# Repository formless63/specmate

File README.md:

A self-hosted engineering workshop for reusable parts, boards, cables, enclosures,
firmware, assemblies, and the physical things built from them.

Define an item once. Pin its exact revision wherever it is used. Carry its sources,
identity and evidence through drawings, build documents, jobs and physical units.
Humans and authorized agents use the same controlled operations.

**Pre-1.0, under active development.** The application is usable from a source-built
installation. Engineering coverage and native-tool support vary by workflow; the
[capability catalog](spec/capabilities.json) describes intended requirements, not a
claim that every capability is qualified. There is no supported stable release yet.

## Inside the workshop

- **A reusable Library:** typed records, immutable revisions, exact references, Where used,
  project collections, searchable identifiers and retained sources.
- **Cables and harnesses:** connector faces, conductor mapping, manual graph editing,
  stock cross-sections and 3D inspection, preparation and test documents.
- **Boards and devices:** declared board connectivity, source-linked native intake,
  component populations, firmware targets, assembly trees and scene inspection.
- **Make and evidence:** BOM and material plans, stock reservations and consumption,
  physical units, retained documents, build receipts and reviewed evidence.
- **Controlled automation:** session-based APIs and MCP, durable Temporal workflows,
  and optional isolated runners with explicit tool and recipe approval.

Unknown dimensions and unverified behavior stay visible. A successful render, check or
build is not physical qualification. See the [product specification](docs/PRODUCT.md)
and [engineering model](docs/DOMAIN.md).

## A look around

The screenshots below show actual application views with synthetic demonstration data.
They do not show customer designs or establish physical qualification.

| Wire-stock construction | Board connectivity |
| --- | --- |
|  |  |

[Screenshot provenance](docs/assets/screenshots/README.md).

## Run it yourself

You need Linux, Docker Engine with the Compose plugin, Git and Python 3. Images are
built from this checkout; no published Specmate image or external account is required.
From a clone of this repository:

```bash
specmate_stack="$HOME/stacks/specmate"
install -d -m 0700 "$specmate_stack"
cp compose.example.yaml "$specmate_stack/compose.yaml"
python3 deploy/configure.py --output "$specmate_stack/.env"
cd "$specmate_stack"
docker compose config -q
docker compose build
docker compose up -d --wait
docker compose exec app python manage.py owner_setup_token
```

Open **http://localhost:8080**, enter the single-use setup token and create your local
owner account. Temporal's operator UI is at http://localhost:8081. Both bind to loopback
by default. Keep the generated `.env` and persistent volumes: they belong to this
installation. The configuration generator refuses to overwrite existing credentials.
The default Compose names are fixed; use a dedicated Docker host or review names,
ports and volumes before running more than one installation.

The [installation guide](deploy/README.md) covers readiness, HTTPS/reverse proxies,
backup and same-version restore, and optional native execution. Build downloads require
network access to pinned image and dependency registries. Native execution is disabled
until explicitly configured; importing a source does not execute it.

## Architecture and contributing

Django/Python owns engineering operations and authorization. React/TypeScript provides
the interface; PostgreSQL and a content-addressed artifact store retain state; Temporal
coordinates durable jobs. The default installation has six services and an optional
runner. No SaaS, AI provider, ERP or email provider is a required dependency.
See [architecture](docs/ARCHITECTURE.md).

Start with [CONTRIBUTING.md](CONTRIBUTING.md), [AGENTS.md](AGENTS.md), the
[documentation map](docs/README.md), and [development commands](docs/DEVELOPMENT.md).
The lightweight repository checks need Python 3.11 or later:

```bash
python3 scripts/check_guidance.py
python3 scripts/check_public_tree.py
```

Before v1.0.0 there is no historical development-schema compatibility promise. Original
sources and real installation data are never implicitly disposable. See the
[development policy](docs/DEVELOPMENT.md).

## Rights

The original application code and documentation are AGPL-3.0-only unless a file declares
otherwise. Third-party code and engineering assets retain their terms. See
[LICENSING.md](LICENSING.md) and [NOTICE](NOTICE).

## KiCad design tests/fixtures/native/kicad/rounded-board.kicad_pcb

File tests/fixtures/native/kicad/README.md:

# Original synthetic KiCad fixtures

`two-net-board.kicad_pcb` is an original, deliberately simple board authored by
`toolpacks/kicad/generate_fixture.py` using the pinned KiCad 10.0.6 image. It uses
embedded original footprints, no external library assets, and stable UUIDs.
The native board format is `20260206`. The fixture files and generator use the
repository's AGPL-3.0-only license.

The board has a 40 × 25 mm outline, 1.6 mm thickness, and four unplated 2 mm
mounting holes at (3, 3), (37, 3), (3, 22), and (37, 22) mm. J1 and R1 each have
two 2 × 2 mm pads. Two 0.5 mm tracks run horizontally from x=10 to x=25 mm at
y=10 and y=15 mm. The first connects J1.1 to R1.1 on N1; the second connects
J1.2 to R1.2 on N2. R1 has value `1k`; its component passage remains separate
from the copper nets. Coordinates follow KiCad's x-right, y-down frame.

The acceptance facts live independently in `tests/fixtures/board-expectations.json`.
The generator does not read that expectation file, and the checker must derive
facts from the native board before comparing them. Preserve that separation when
changing either side. Successful DRC does not qualify a physical design; there is
no schematic, sourced component, electrical rating or manufacturing process here.

`invalid-board.kicad_pcb` deliberately has an unknown item and an unclosed root.
It exercises rejection by the real parser; it is not a valid engineering source.
Do not repair it into a successful input.

See `toolpacks/kicad/README.md` for the pinned environment and regeneration.

`rounded-board.kicad_pcb` is the same original board with a different `Edge.Cuts`
outline: a 40 × 25 mm rectangle with four 4 mm radius corner arcs (arcs authored
as start, mid, end) and one 3 mm radius circular cutout centerd at (20, 12.5) mm.
Expected exact values are derived analytically in `backend/tests/test_pcb_outline_arcs.py`:
net area = 1000 − 4·(4 − π)·4² − π·3² mm², bounds 0, 0 to 40, 25.

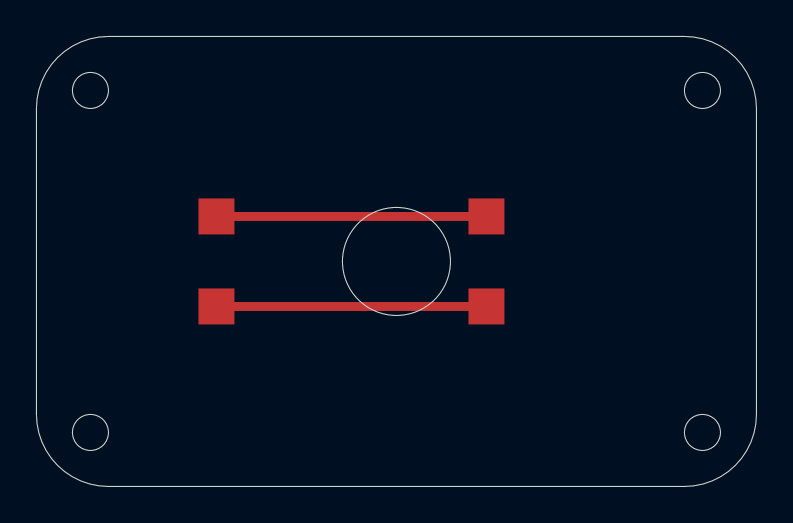
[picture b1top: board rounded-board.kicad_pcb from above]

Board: 2 copper layers, 40.0 x 25.0 mm, 6 parts (0 on the bottom side), 2 nets.

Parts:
H1: MountingHole_2mm; Synthetic_H1
H2: MountingHole_2mm; Synthetic_H2
H3: MountingHole_2mm; Synthetic_H3
H4: MountingHole_2mm; Synthetic_H4
J1: CONN_2; Synthetic_J1
R1: 1k; Synthetic_R1

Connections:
N1: J1.1, R1.1
N2: J1.2, R1.2
